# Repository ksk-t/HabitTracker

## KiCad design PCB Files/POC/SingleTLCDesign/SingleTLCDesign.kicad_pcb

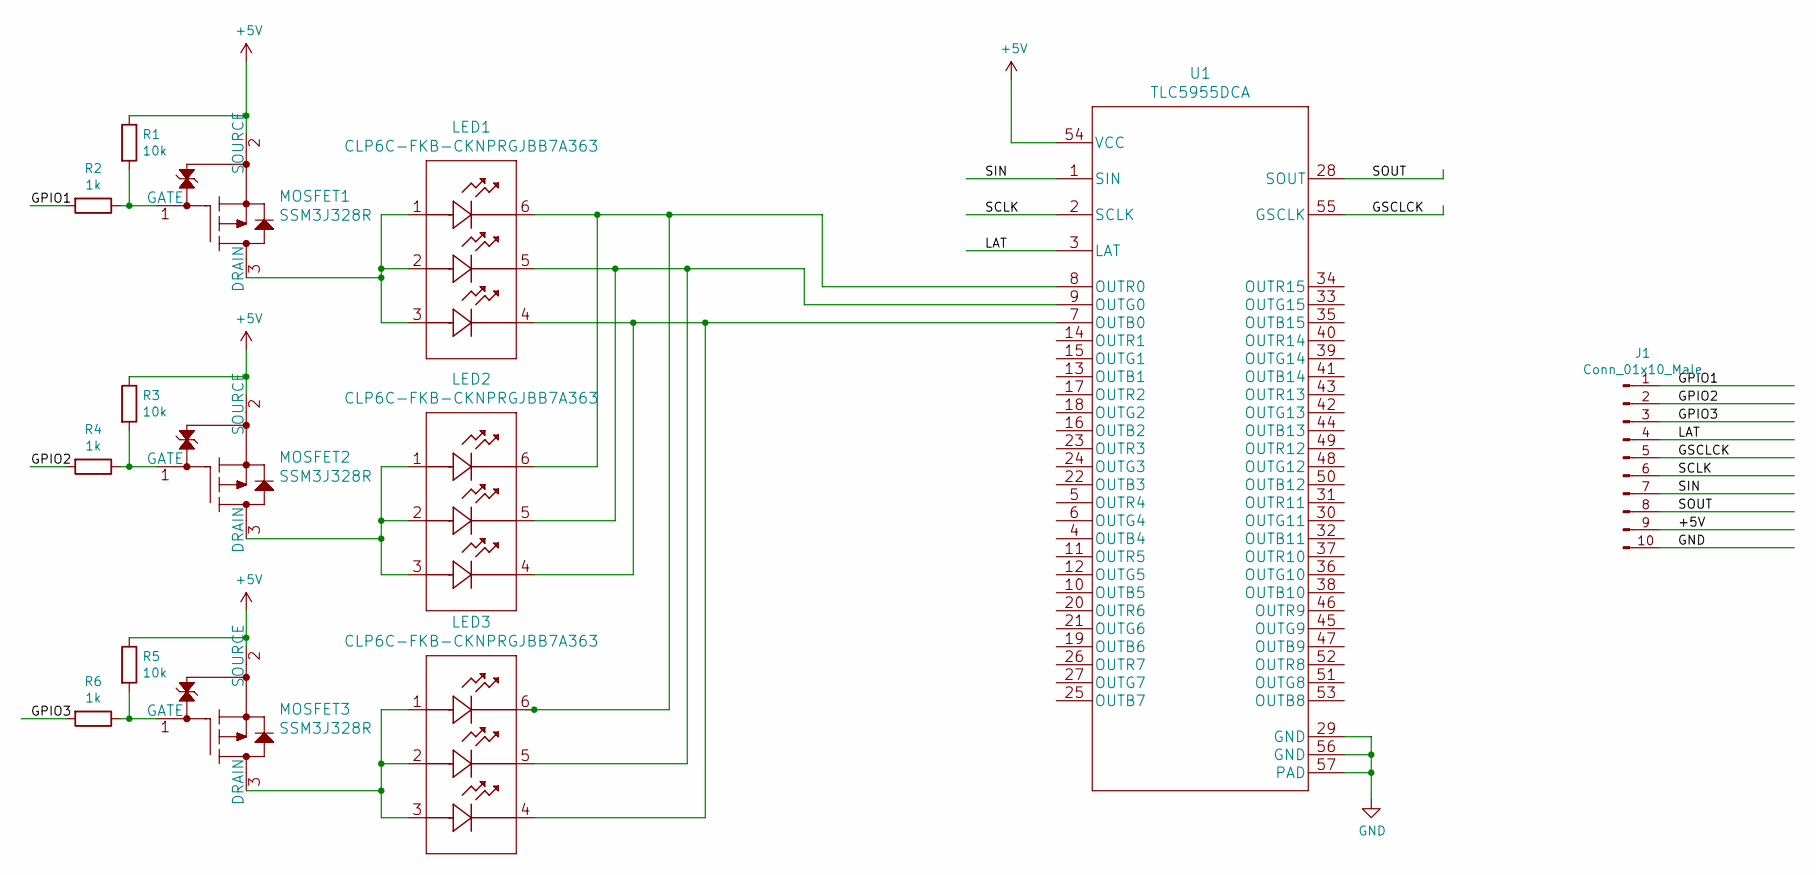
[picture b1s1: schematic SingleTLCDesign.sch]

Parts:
J1: Conn_01x10_Male; PinHeader_1x10_P2.54mm_Vertical
LED1, LED2, LED3: CLP6C-FKB-CKNPRGJBB7A363
MOSFET1, MOSFET2, MOSFET3: SSM3J328R
R1, R3, R5: 10k; R_0805_2012Metric_Pad1.20x1.40mm_HandSolder
R2, R4, R6: 1k; R_0805_2012Metric_Pad1.20x1.40mm_HandSolder
U1: TLC5955DCA

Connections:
+5V: J1.9, MOSFET1.2 (SOURCE), MOSFET2.2 (SOURCE), MOSFET3.2 (SOURCE), R1.1, R3.1, R5.1, U1.54 (VCC)
/GPIO1: J1.1, R2.2
/GPIO2: J1.2, R4.2
/GPIO3: J1.3, R6.2
/GSCLCK: J1.5, U1.55 (GSCLK)
/LAT: J1.4, U1.3 (LAT)
/SCLK: J1.6, U1.2 (SCLK)
/SIN: J1.7, U1.1 (SIN)
/SOUT: J1.8, U1.28 (SOUT)
GND: J1.10, U1.29 (GND), U1.56 (GND), U1.57 (PAD)
unnamed: LED1.1, LED1.2, LED1.3, MOSFET1.3 (DRAIN)
unnamed: LED1.4, LED2.4, LED3.4, U1.7 (OUTB0)
unnamed: LED1.5, LED2.5, LED3.5, U1.9 (OUTG0)
unnamed: LED1.6, LED2.6, LED3.6, U1.8 (OUTR0)
unnamed: LED2.1, LED2.2, LED2.3, MOSFET2.3 (DRAIN)
unnamed: LED3.1, LED3.2, LED3.3, MOSFET3.3 (DRAIN)
unnamed: MOSFET1.1 (GATE), R1.2, R2.1
unnamed: MOSFET2.1 (GATE), R3.2, R4.1
unnamed: MOSFET3.1 (GATE), R5.2, R6.1

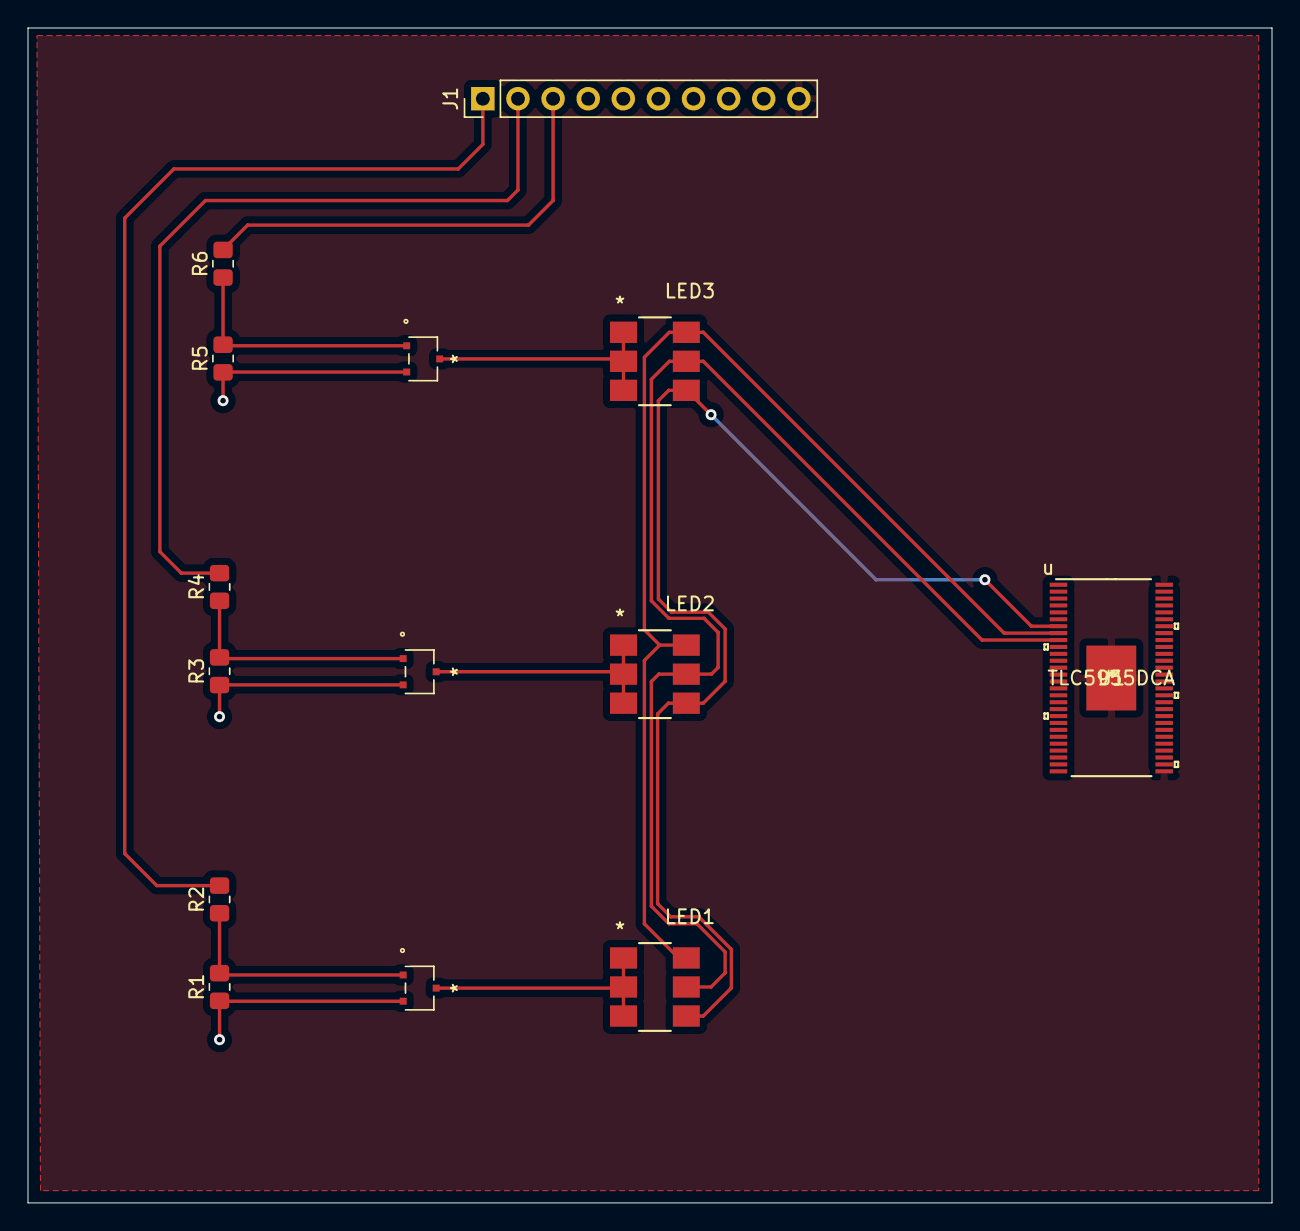
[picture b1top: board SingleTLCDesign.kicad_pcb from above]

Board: 2 copper layers, 90.0 x 85.0 mm, 14 parts (0 on the bottom side), 19 nets.

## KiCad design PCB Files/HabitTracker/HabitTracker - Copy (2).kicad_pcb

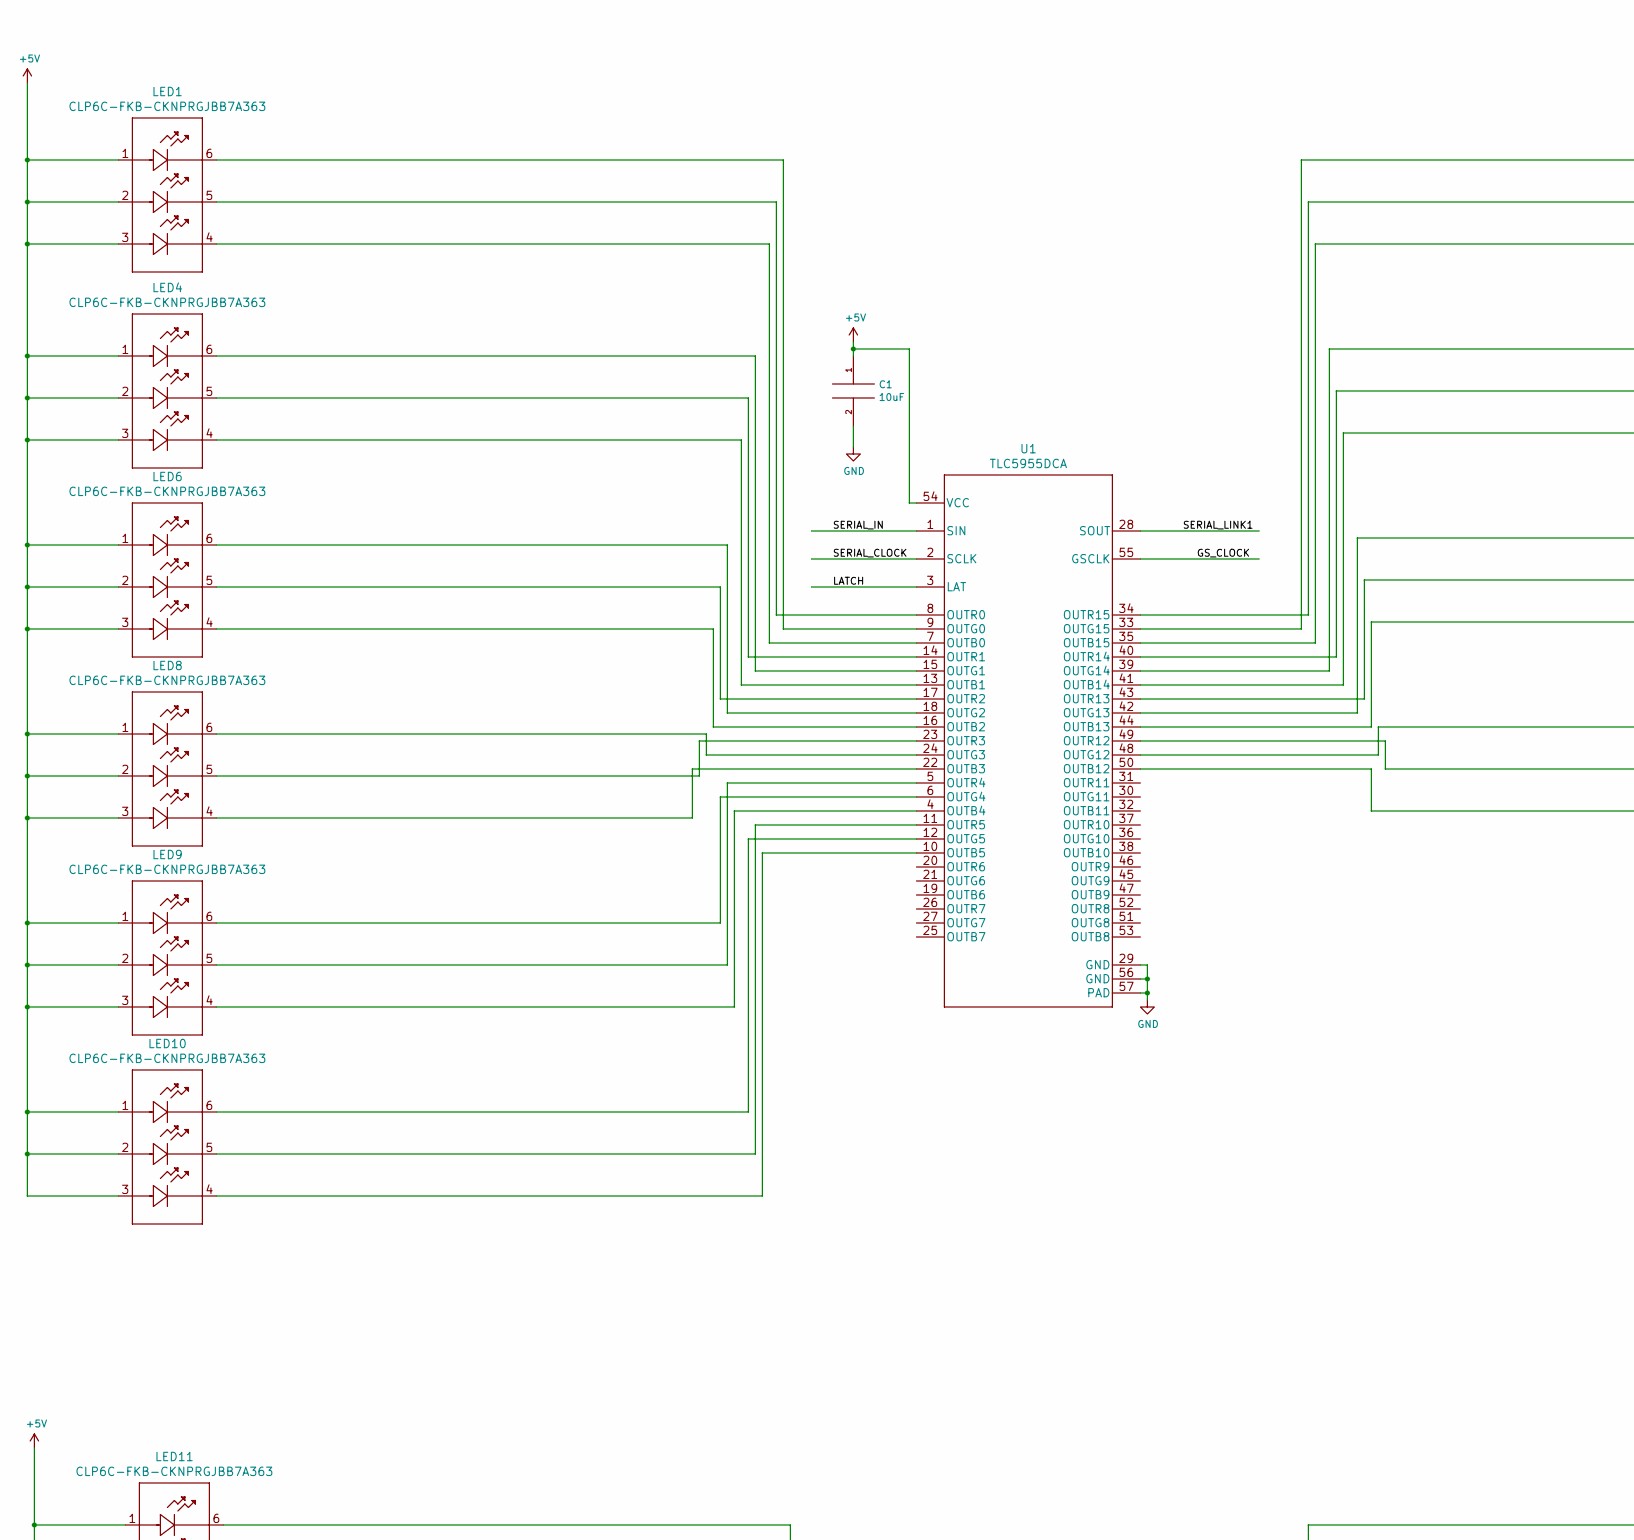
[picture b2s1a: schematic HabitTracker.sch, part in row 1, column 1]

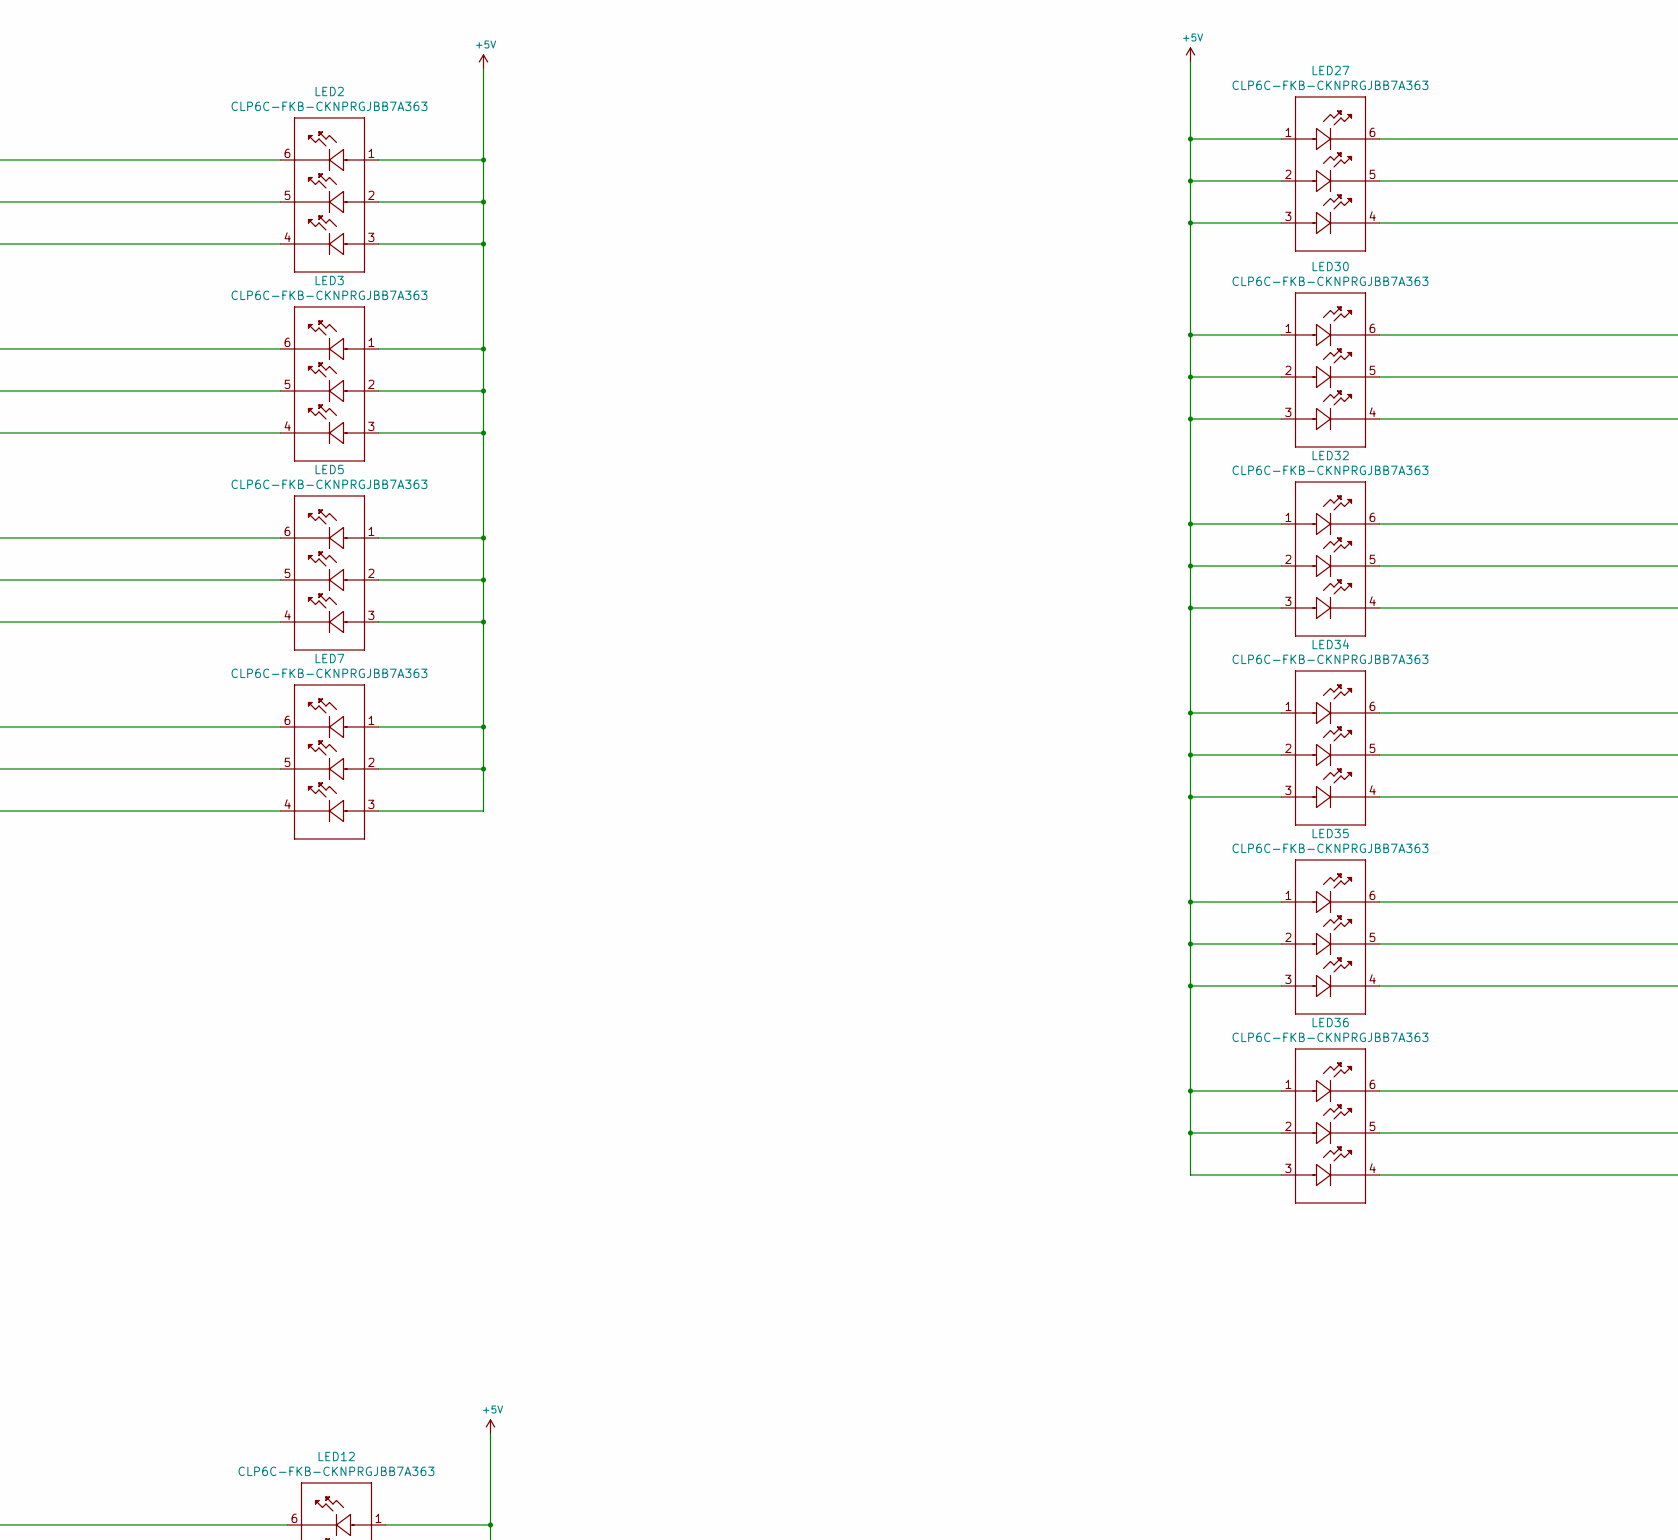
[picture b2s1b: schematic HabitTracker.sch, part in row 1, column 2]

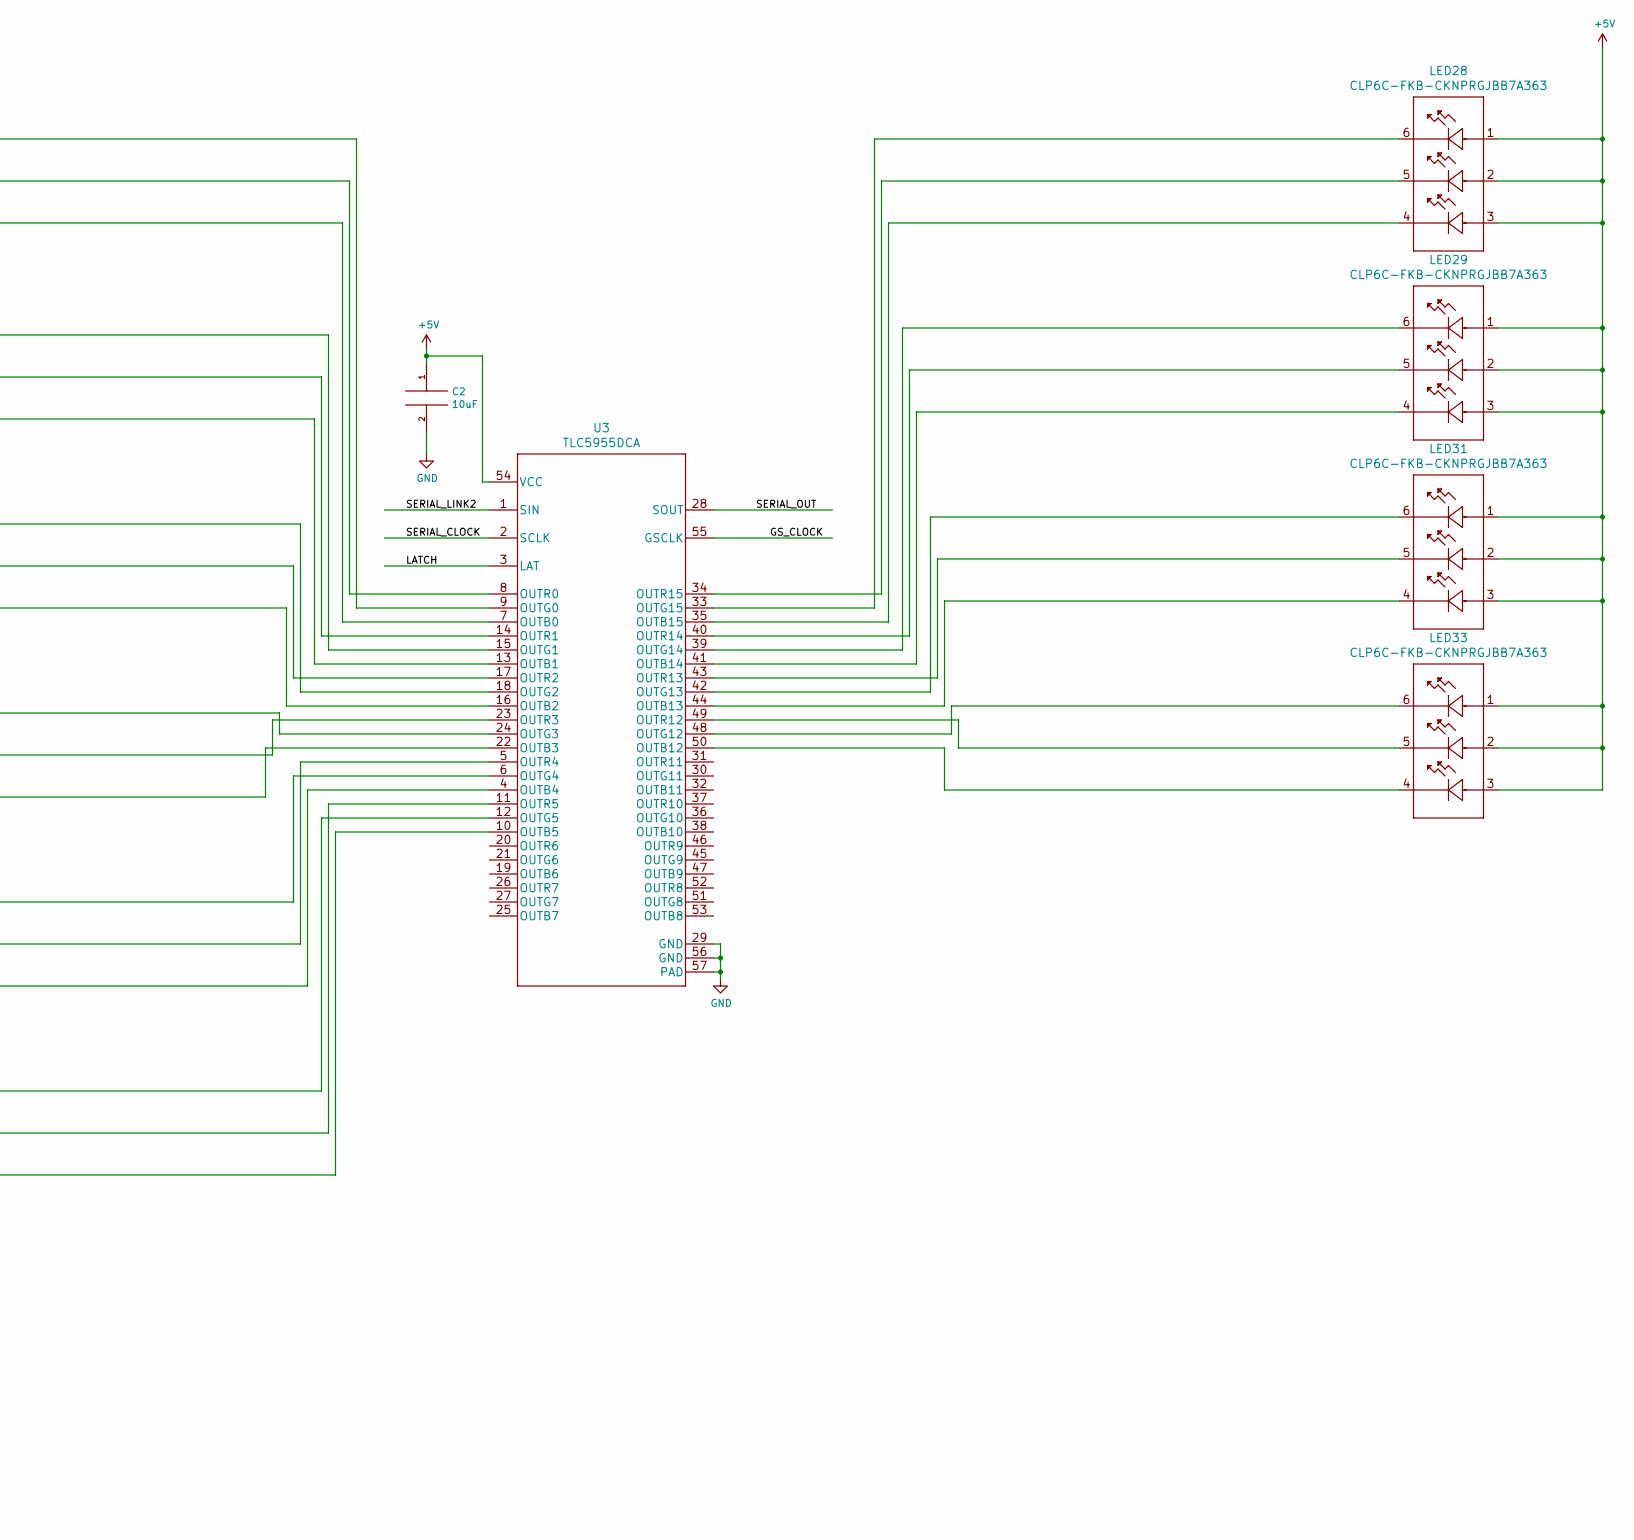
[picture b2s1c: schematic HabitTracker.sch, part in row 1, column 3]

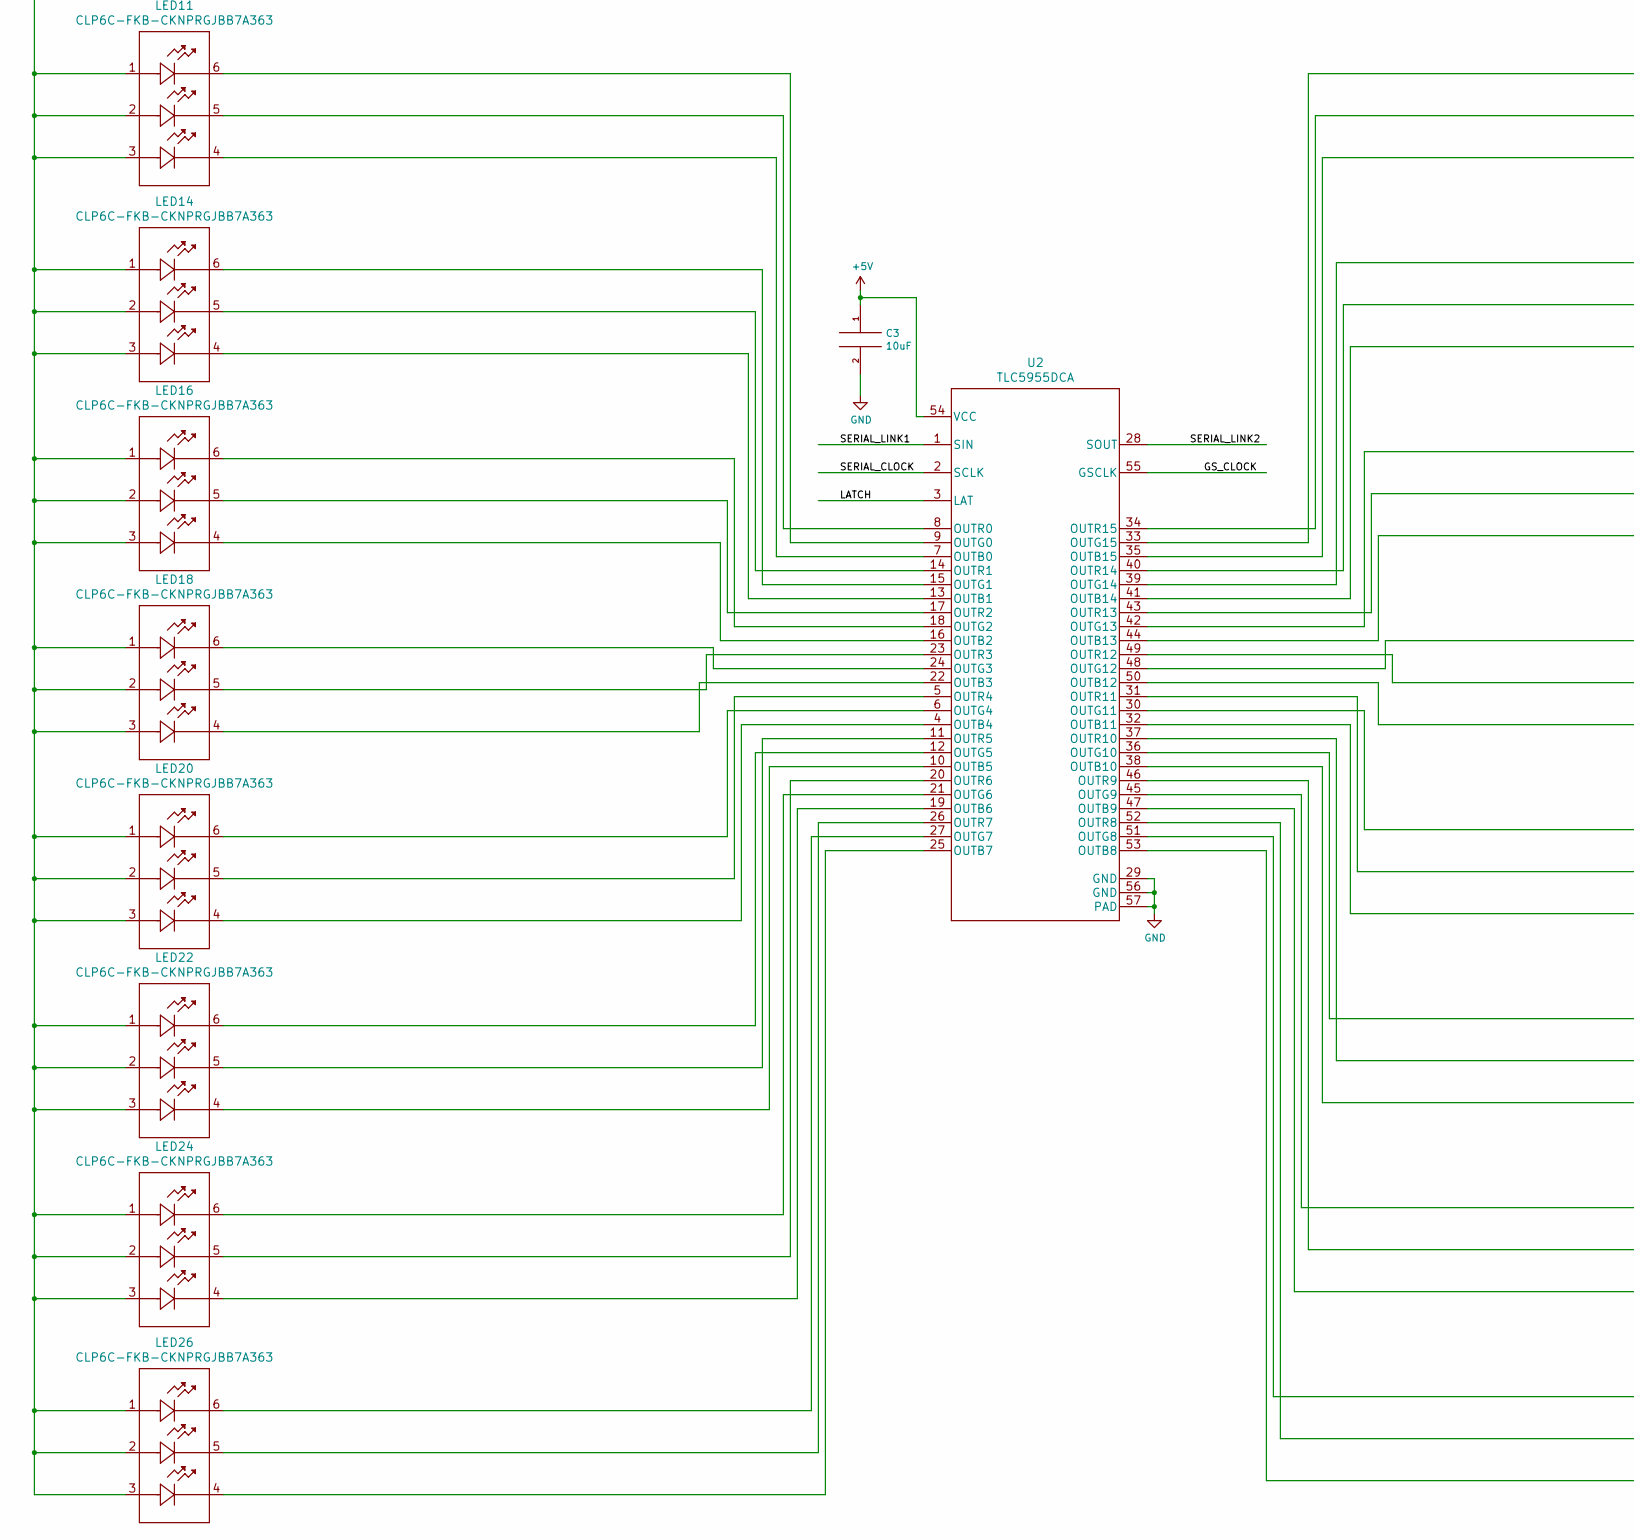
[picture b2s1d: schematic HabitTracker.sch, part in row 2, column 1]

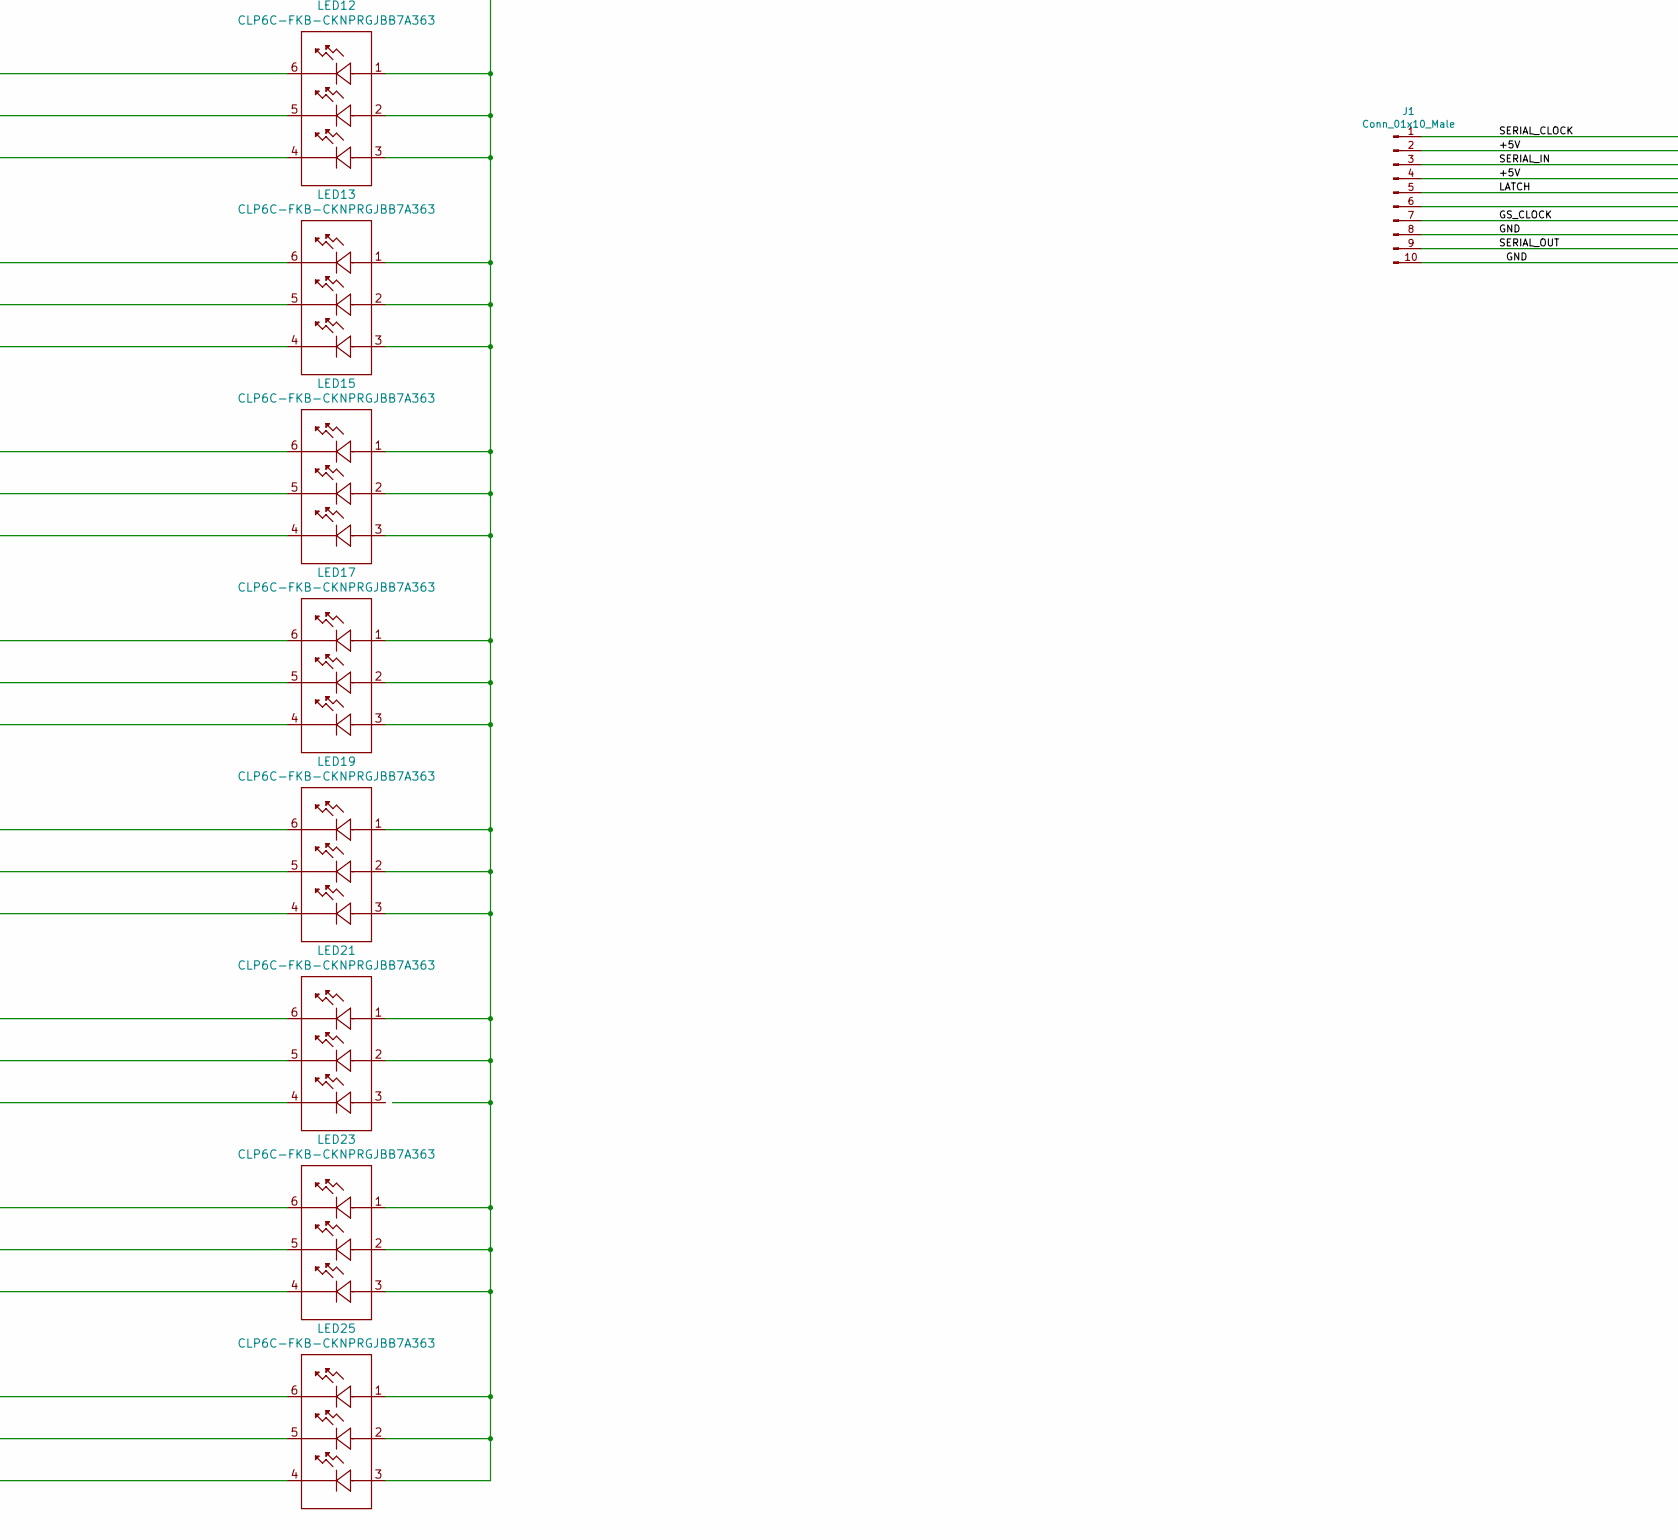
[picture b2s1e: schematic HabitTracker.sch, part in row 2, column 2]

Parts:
C1, C2, C3: 10uF; C_0805_2012Metric
J1: Conn_01x10_Male; PinSocket_2x05_P2.54mm_Vertical
LED1, LED2, LED3, LED4, LED5, LED6, LED7, LED8, LED9, LED10, LED11, LED12, LED13, LED14, LED15, LED16, LED17, LED18, LED19, LED20, LED21, LED22, LED23, LED24, LED25, LED26, LED27, LED28, LED29, LED30, LED31, LED32, LED33, LED34, LED35, LED36: CLP6C-FKB-CKNPRGJBB7A363
U1, U2, U3: TLC5955DCA

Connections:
+5V: C1.1, C2.1, C3.1, J1.2, J1.4, LED1.1, LED1.2, LED1.3, LED2.1, LED2.2, LED2.3, LED3.1, LED3.2, LED3.3, LED4.1, LED4.2, LED4.3, LED5.1, LED5.2, LED5.3, LED6.1, LED6.2, LED6.3, LED7.1, LED7.2, LED7.3, LED8.1, LED8.2, LED8.3, LED9.1, LED9.2, LED9.3, LED10.1, LED10.2, LED10.3, LED11.1, LED11.2, LED11.3, LED12.1, LED12.2, LED12.3, LED13.1, LED13.2, LED13.3, LED14.1, LED14.2, LED14.3, LED15.1, LED15.2, LED15.3, LED16.1, LED16.2, LED16.3, LED17.1, LED17.2, LED17.3, LED18.1, LED18.2, LED18.3, LED19.1, LED19.2, LED19.3, LED20.1, LED20.2, LED20.3, LED21.1, LED21.2, LED22.1, LED22.2, LED22.3, LED23.1, LED23.2, LED23.3, LED24.1, LED24.2, LED24.3, LED25.1, LED25.2, LED25.3, LED26.1, LED26.2, LED26.3, LED27.1, LED27.2, LED27.3, LED28.1, LED28.2, LED28.3, LED29.1, LED29.2, LED29.3, LED30.1, LED30.2, LED30.3, LED31.1, LED31.2, LED31.3, LED32.1, LED32.2, LED32.3, LED33.1, LED33.2, LED33.3, LED34.1, LED34.2, LED34.3, LED35.1, LED35.2, LED35.3, LED36.1, LED36.2, LED36.3, U1.54 (VCC), U2.54 (VCC), U3.54 (VCC)
/GS_CLOCK: J1.7, U1.55 (GSCLK), U2.55 (GSCLK), U3.55 (GSCLK)
/LATCH: J1.5, U1.3 (LAT), U2.3 (LAT), U3.3 (LAT)
/SERIAL_CLOCK: J1.1, U1.2 (SCLK), U2.2 (SCLK), U3.2 (SCLK)
/SERIAL_IN: J1.3, U1.1 (SIN)
/SERIAL_LINK1: U1.28 (SOUT), U2.1 (SIN)
/SERIAL_LINK2: U2.28 (SOUT), U3.1 (SIN)
/SERIAL_OUT: J1.9, U3.28 (SOUT)
GND: C1.2, C2.2, C3.2, J1.8, J1.10, U1.29 (GND), U1.56 (GND), U1.57 (PAD), U2.29 (GND), U2.56 (GND), U2.57 (PAD), U3.29 (GND), U3.56 (GND), U3.57 (PAD)
unnamed: LED1.4, U1.7 (OUTB0)
unnamed: LED1.5, U1.8 (OUTR0)
unnamed: LED1.6, U1.9 (OUTG0)
unnamed: LED2.4, U1.35 (OUTB15)
unnamed: LED2.5, U1.34 (OUTR15)
unnamed: LED2.6, U1.33 (OUTG15)
unnamed: LED3.4, U1.41 (OUTB14)
unnamed: LED3.5, U1.40 (OUTR14)
unnamed: LED3.6, U1.39 (OUTG14)
unnamed: LED4.4, U1.13 (OUTB1)
unnamed: LED4.5, U1.14 (OUTR1)
unnamed: LED4.6, U1.15 (OUTG1)
unnamed: LED5.4, U1.44 (OUTB13)
unnamed: LED5.5, U1.43 (OUTR13)
unnamed: LED5.6, U1.42 (OUTG13)
unnamed: LED6.4, U1.16 (OUTB2)
unnamed: LED6.5, U1.17 (OUTR2)
unnamed: LED6.6, U1.18 (OUTG2)
unnamed: LED7.4, U1.50 (OUTB12)
unnamed: LED7.5, U1.49 (OUTR12)
unnamed: LED7.6, U1.48 (OUTG12)
unnamed: LED8.4, U1.22 (OUTB3)
unnamed: LED8.5, U1.23 (OUTR3)
unnamed: LED8.6, U1.24 (OUTG3)
unnamed: LED9.4, U1.4 (OUTB4)
unnamed: LED9.5, U1.5 (OUTR4)
unnamed: LED9.6, U1.6 (OUTG4)
unnamed: LED10.4, U1.10 (OUTB5)
unnamed: LED10.5, U1.11 (OUTR5)
unnamed: LED10.6, U1.12 (OUTG5)
unnamed: LED11.4, U2.7 (OUTB0)
unnamed: LED11.5, U2.8 (OUTR0)
unnamed: LED11.6, U2.9 (OUTG0)
unnamed: LED12.4, U2.35 (OUTB15)
unnamed: LED12.5, U2.34 (OUTR15)
unnamed: LED12.6, U2.33 (OUTG15)
unnamed: LED13.4, U2.41 (OUTB14)
unnamed: LED13.5, U2.40 (OUTR14)
unnamed: LED13.6, U2.39 (OUTG14)
unnamed: LED14.4, U2.13 (OUTB1)
unnamed: LED14.5, U2.14 (OUTR1)
unnamed: LED14.6, U2.15 (OUTG1)
unnamed: LED15.4, U2.44 (OUTB13)
unnamed: LED15.5, U2.43 (OUTR13)
unnamed: LED15.6, U2.42 (OUTG13)
unnamed: LED16.4, U2.16 (OUTB2)
unnamed: LED16.5, U2.17 (OUTR2)
unnamed: LED16.6, U2.18 (OUTG2)
unnamed: LED17.4, U2.50 (OUTB12)
unnamed: LED17.5, U2.49 (OUTR12)
unnamed: LED17.6, U2.48 (OUTG12)
unnamed: LED18.4, U2.22 (OUTB3)
unnamed: LED18.5, U2.23 (OUTR3)
unnamed: LED18.6, U2.24 (OUTG3)
unnamed: LED19.4, U2.32 (OUTB11)
unnamed: LED19.5, U2.31 (OUTR11)
unnamed: LED19.6, U2.30 (OUTG11)
unnamed: LED20.4, U2.4 (OUTB4)
unnamed: LED20.5, U2.5 (OUTR4)
unnamed: LED20.6, U2.6 (OUTG4)
unnamed: LED21.4, U2.38 (OUTB10)
unnamed: LED21.5, U2.37 (OUTR10)
unnamed: LED21.6, U2.36 (OUTG10)
unnamed: LED22.4, U2.10 (OUTB5)
unnamed: LED22.5, U2.11 (OUTR5)
unnamed: LED22.6, U2.12 (OUTG5)
unnamed: LED23.4, U2.47 (OUTB9)
unnamed: LED23.5, U2.46 (OUTR9)
unnamed: LED23.6, U2.45 (OUTG9)
unnamed: LED24.4, U2.19 (OUTB6)
unnamed: LED24.5, U2.20 (OUTR6)
unnamed: LED24.6, U2.21 (OUTG6)
unnamed: LED25.4, U2.53 (OUTB8)
unnamed: LED25.5, U2.52 (OUTR8)
unnamed: LED25.6, U2.51 (OUTG8)
unnamed: LED26.4, U2.25 (OUTB7)
unnamed: LED26.5, U2.26 (OUTR7)
unnamed: LED26.6, U2.27 (OUTG7)
unnamed: LED27.4, U3.7 (OUTB0)
unnamed: LED27.5, U3.8 (OUTR0)
unnamed: LED27.6, U3.9 (OUTG0)
unnamed: LED28.4, U3.35 (OUTB15)
unnamed: LED28.5, U3.34 (OUTR15)
unnamed: LED28.6, U3.33 (OUTG15)
unnamed: LED29.4, U3.41 (OUTB14)
unnamed: LED29.5, U3.40 (OUTR14)
unnamed: LED29.6, U3.39 (OUTG14)
unnamed: LED30.4, U3.13 (OUTB1)
unnamed: LED30.5, U3.14 (OUTR1)
unnamed: LED30.6, U3.15 (OUTG1)
unnamed: LED31.4, U3.44 (OUTB13)
unnamed: LED31.5, U3.43 (OUTR13)
unnamed: LED31.6, U3.42 (OUTG13)
unnamed: LED32.4, U3.16 (OUTB2)
unnamed: LED32.5, U3.17 (OUTR2)
unnamed: LED32.6, U3.18 (OUTG2)
unnamed: LED33.4, U3.50 (OUTB12)
unnamed: LED33.5, U3.49 (OUTR12)
unnamed: LED33.6, U3.48 (OUTG12)
unnamed: LED34.4, U3.22 (OUTB3)
unnamed: LED34.5, U3.23 (OUTR3)
unnamed: LED34.6, U3.24 (OUTG3)
unnamed: LED35.4, U3.4 (OUTB4)
unnamed: LED35.5, U3.5 (OUTR4)
unnamed: LED35.6, U3.6 (OUTG4)
unnamed: LED36.4, U3.10 (OUTB5)
unnamed: LED36.5, U3.11 (OUTR5)
unnamed: LED36.6, U3.12 (OUTG5)

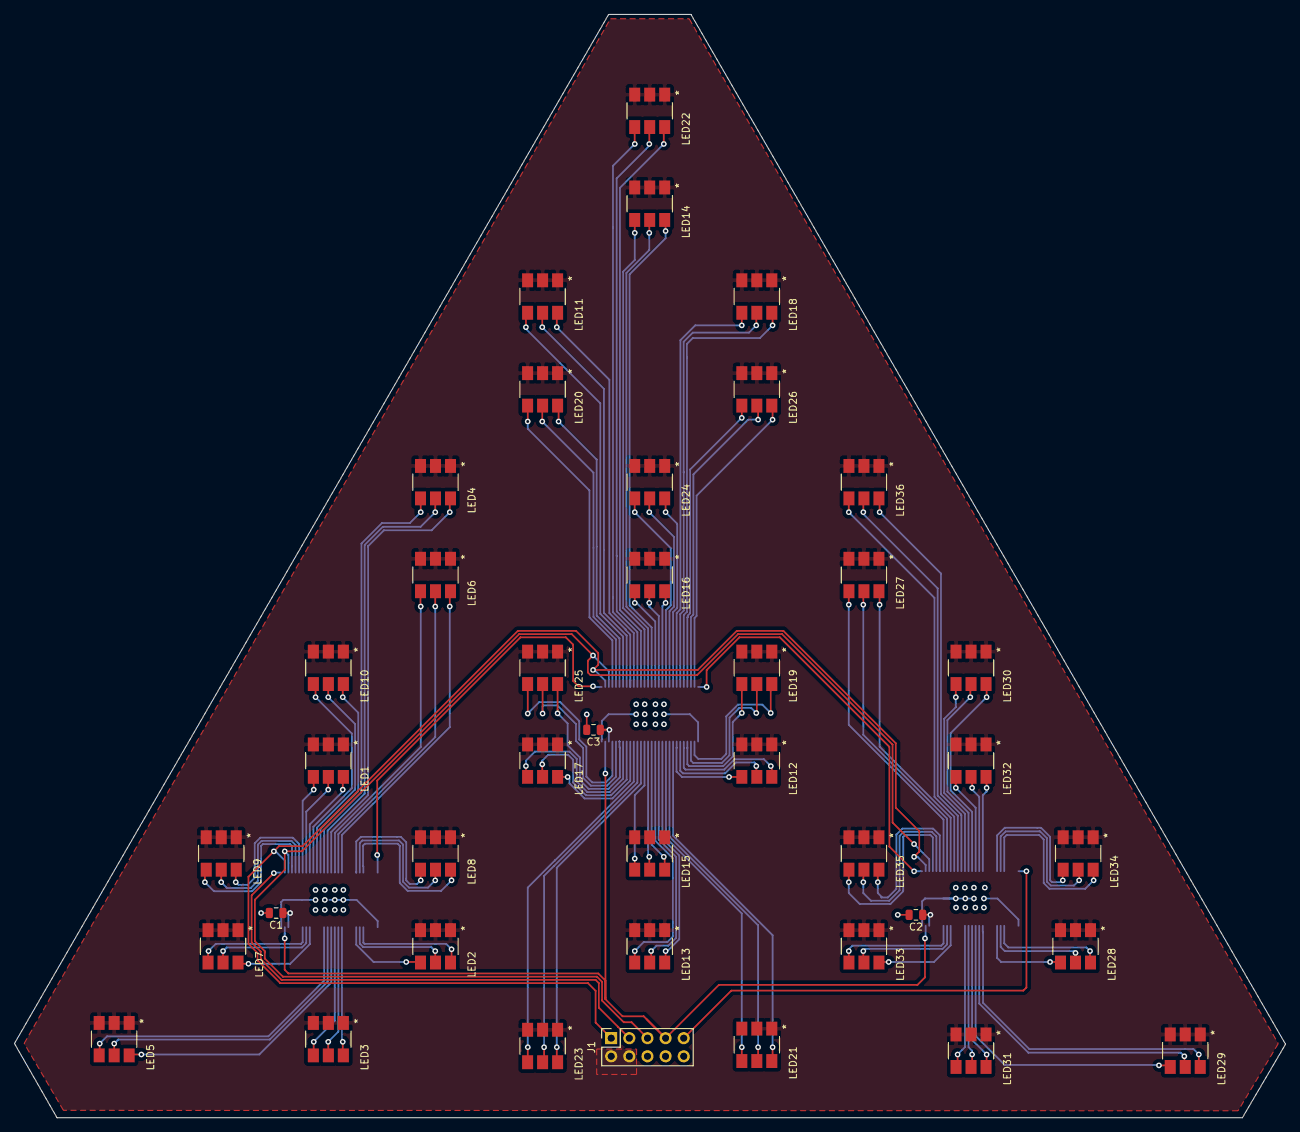
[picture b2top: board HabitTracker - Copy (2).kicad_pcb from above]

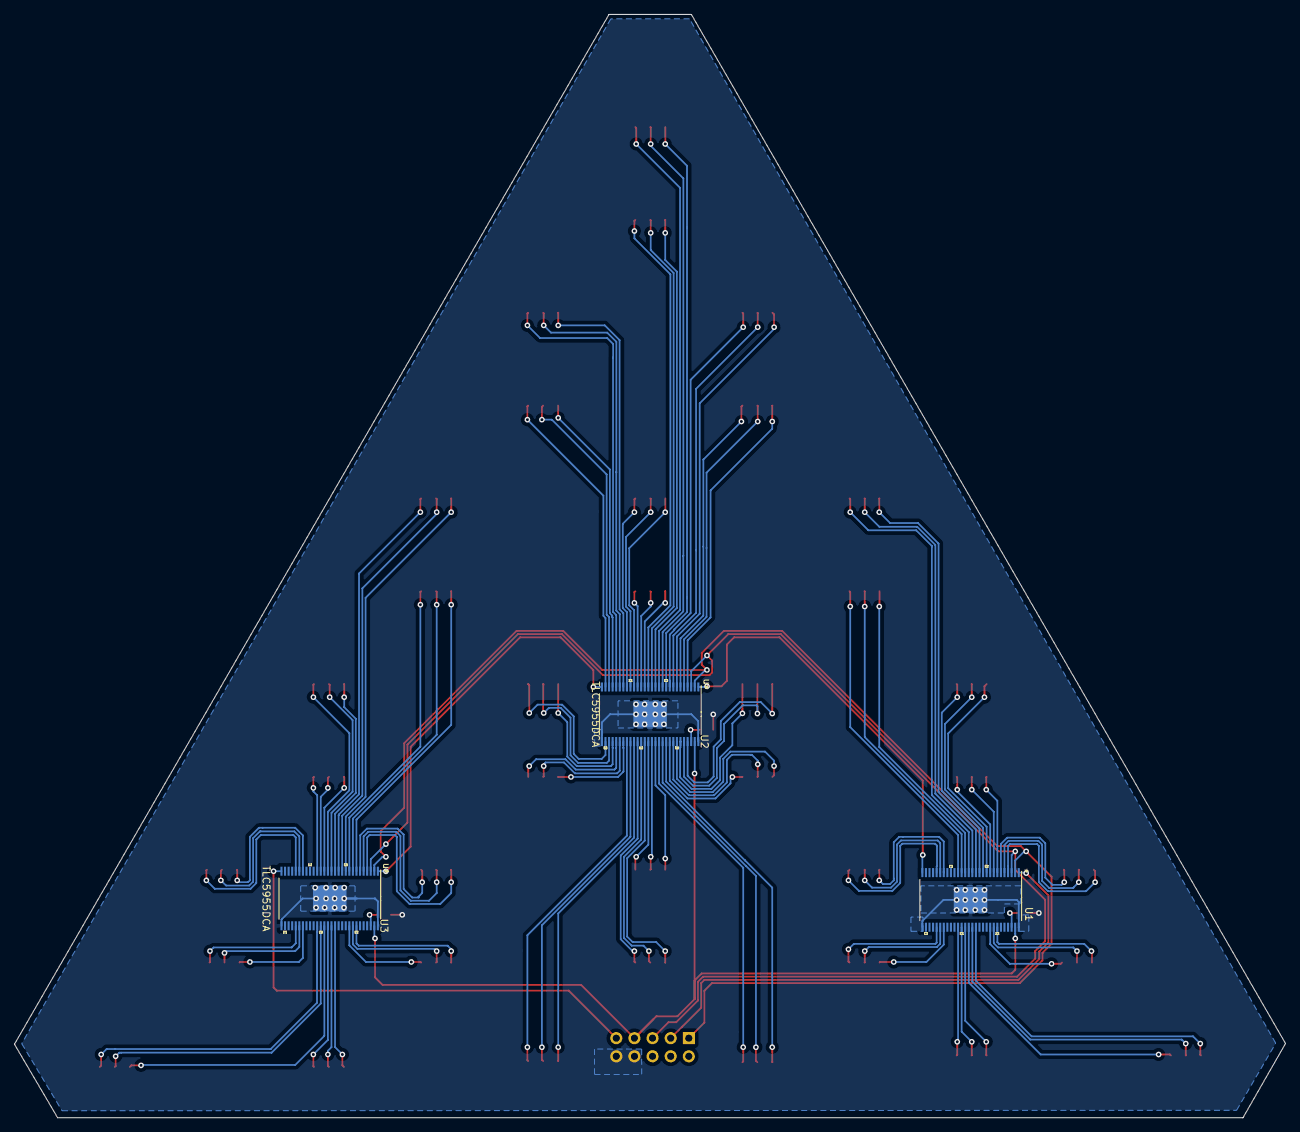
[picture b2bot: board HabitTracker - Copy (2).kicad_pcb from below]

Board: 2 copper layers, 178.0 x 154.5 mm, 43 parts (3 on the bottom side), 117 nets.

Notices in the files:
parts and their libraries:
Copyright 2016 Accelerated Designs. All rights reserved.
